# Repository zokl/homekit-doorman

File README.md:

# Doorman HomeKit System
System of a doorbell and smart lock integration into Apple HomeKit. The project platform is ESP8266 - [WeMos D1 Mini](https://wiki.wemos.cc/products:d1:d1_mini). Target door phone system is [Fermax](https://github.com/zokl/homekit-doorman/blob/master/doc/Fermax%20CityMax%20Universal%20%20Intercom%20Handset%20Data%20Sheet.pdf).

The SW part of the project is based on https://github.com/maximkulkin/esp-homekit-demo and https://github.com/pfalcon/esp-open-sdk.

## Fermax phone interconnection

Fermax phone signals:
* **RingDet** - ringing detector
   * **3** - common (- on PCB)
   * **4** - call (+ on PCB)
* **Lock** - door lock control
   * **1** - door opener and microphone supply (+ on PCB)
   * **3** - common (+ on PCB)

## Initial configuration

The initial configuration could be modified in the file [config.h](https://github.com/zokl/homekit-doorman/blob/master/src/config.h).

### HomeKit Access Parameters

* HOMEKIT_PASSWORD - "111-00-111"
* HOMEKIT_SETUP_ID - "1QJ9"

### System Parameters

* The GPIO pin that is connected to a relay - WeMos D1 Mini - Pin D1
* The GPIO pin that is connected to a LED - WeMos D1 Mini - Pin D4 (Internal Blue LED)
* The GPIO pin that is connected to a button - WeMos D1 Mini - Pin D3
  * Button for door open or factory reset
* The GPIO pin that is connected to a door bell - WeMos D1 Mini - Pin D2
  * Door bell detection - iOS notify as moving
* Timeout in seconds to open lock for - 5 seconds
* Button timeout for log press - 10000 ms (factory reset)
  * Shorter press = open the door
* Doorbell notify timeout - 3000 ms
  * After this timeout system disarm the door bell notification

## PCB Design

PCB is designed for using in DIN rail box [Z103J ABS V0 KRADEX](https://github.com/zokl/homekit-doorman/blob/master/doc/dsh.627-099.1.pdf) with AC/DC power supply [MEAN WELL DR-15-5](https://github.com/zokl/homekit-doorman/blob/master/doc/dsh.751-263.1.pdf). **The system can be powered only by 5V DC!!!**

## Compilation and deployment
All binary files are in ```bin``` directory.

### Flash process

```
esptool.py write_flash -fs 1MB -fm dout -ff 40m 0x0 rboot.bin 0x1000 blank_config.bin 0x2000 doorman.bin
```

* [rboot.bin](https://github.com/zokl/homekit-doorman/blob/master/bin/rboot.bin) - boot loader
* [blank_config.bin](https://github.com/zokl/homekit-doorman/blob/master/bin/blank_config.bin) - blank config partition
* [doorman.bin](https://github.com/zokl/homekit-doorman/blob/master/bin/doorman_20200307.bin) - firmware

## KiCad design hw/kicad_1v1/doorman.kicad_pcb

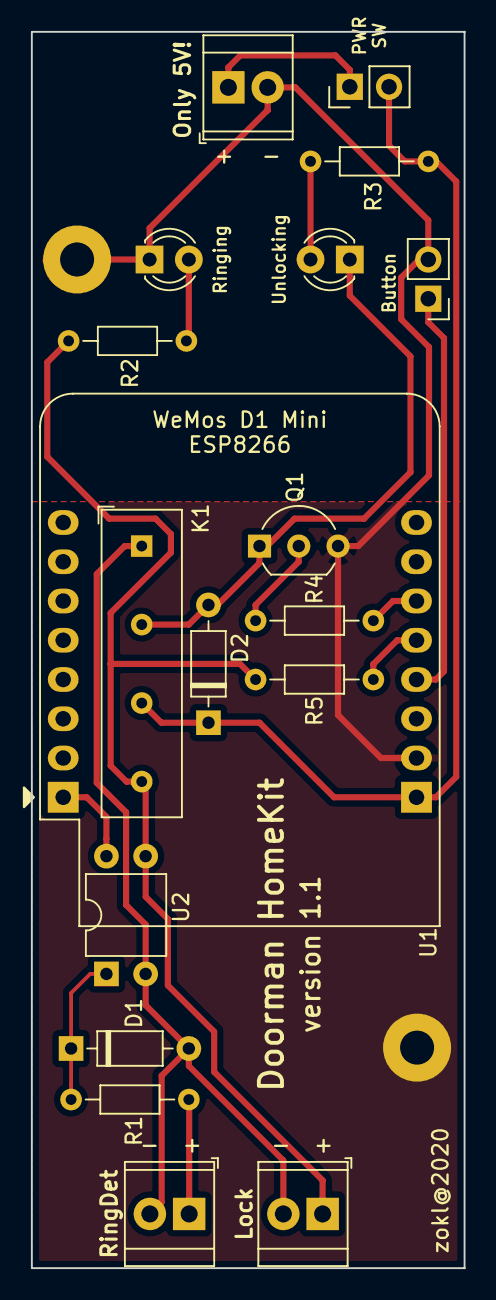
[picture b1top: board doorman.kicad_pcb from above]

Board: 2 copper layers, 28.0 x 80.0 mm, 20 parts (0 on the bottom side), 15 nets.

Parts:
 : Jumper; PinHeader_1x02_P2.54mm_Vertical
Button: Button; PinHeader_1x02_P2.54mm_Vertical
D1, D2: 1N4148; D_DO-35_SOD27_P7.62mm_Horizontal
H1, H2: MountingHole_Pad; MountingHole_2.2mm_M2_Pad
J1: Ring Detection; TerminalBlock_TE_282834-2_1x02_P2.54mm_Horizontal
J2: Lock; TerminalBlock_TE_282834-2_1x02_P2.54mm_Horizontal
J3: Power Supply; TerminalBlock_TE_282834-2_1x02_P2.54mm_Horizontal
K1: S1A05; Relay_SPST_StandexMeder_SIL_Form1A
Q1: BC337; TO-92_Inline_Wide
R1: 680R; R_Axial_DIN0204_L3.6mm_D1.6mm_P7.62mm_Horizontal
R2, R3: 380R; R_Axial_DIN0204_L3.6mm_D1.6mm_P7.62mm_Horizontal
R4, R5: 1k; R_Axial_DIN0204_L3.6mm_D1.6mm_P7.62mm_Horizontal
Ringing: Green; LED_D3.0mm
U1: WeMos_mini; WEMOS_D1_mini_light
U2: PC817; DIP-4_W7.62mm
Unlocking: Red; LED_D3.0mm

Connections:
+3V3: U1.16, U2.4
+5V: .2, D2.1, K1.5, R3.2, U1.1
Butt: Button.1, U1.4
GND: Button.2, H1.1, H2.1, J3.2, Q1.3, Ringing.1, U1.2
Lock: R4.2, U1.6
unnamed: D1.1, R1.2, U2.1
unnamed: D2.2, K1.3, Q1.1, Unlocking.1
unnamed: .1, J3.1
unnamed: R2.1, Ringing.2
unnamed: R3.1, Unlocking.2
unnamed: Q1.2, R4.1
PhGND: D1.2, J1.2, J2.2, K1.1, U2.2
PhLock: J2.1, K1.7, R2.2, R5.1, U2.3
PhRing: J1.1, R1.1
RingDet: R5.2, U1.5

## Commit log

2020-01-10 First commit.
2020-01-10 Changes in code structure.
2020-01-10 Add new Initial config info.
2020-01-10 Documentation of the project and its components.
2020-01-10 Binarybootloader for ESP8266 and blank configuration part. for Homekit.
2020-01-10 Minor description update.
2020-01-10 Dorman - HomeKit firmware for ESP8266
2020-01-10 New SDK changes.
2020-01-10 New SDK.
2020-01-10 New device for doorbell.
2020-01-12 Optimization for target GPIO and timing configuration.
2020-01-13 KiCAD PCB proposal.
2020-01-13 KiCAD PCB proposal.Minor description changes.
2020-01-15 New Dorman v 1.0 PCB design.
2020-01-15 PCB Update.
2020-01-16 New PCB mask, new PWR wires size.
2020-01-16 Final PCB.
2020-01-16 PCB production documentation
2020-01-18 Add Doorbell timeout callback.
2020-03-03 Fix the pin description.
2020-03-03 First relase of redesign PCB because of wrong ESP module layout. Partialy fix #2
2020-03-07 New PCB layout. Version 1.1.
    Completly redesigned PCB layout. Fix of wrong Wemos D1 mini layout.
    New antenna position and connectors to external LEDs and BUTTON.
2020-03-07 Change directory structure.
2020-03-07 Remove orphaned files.
2020-03-07 Change description layout. Add cotas.
2020-03-07 Doorman v 1.1 PCB renders.
2020-03-07 Set default homekit password to 111-00-111
2020-03-07 New binary file for doorman. HK PWD: 111-00-111
2020-03-07 Small changes
    - Add schematics picture.
    - Small changes in schematics description.
    - Rename pictures.
2020-03-07 Remove orphan files.
2020-03-07 New datasheets.
2020-03-07 Fotos from real installation.
2020-03-07 Add Fermax Home Phone datasheet and foto.
2020-03-07 Update README.md
    Add Fermax datasheet link.
2020-03-07 Update README.md
    Add Fermax phone interconnection.
2020-03-07 Add Door Opener proposal.
2021-02-03 Fixes #4
